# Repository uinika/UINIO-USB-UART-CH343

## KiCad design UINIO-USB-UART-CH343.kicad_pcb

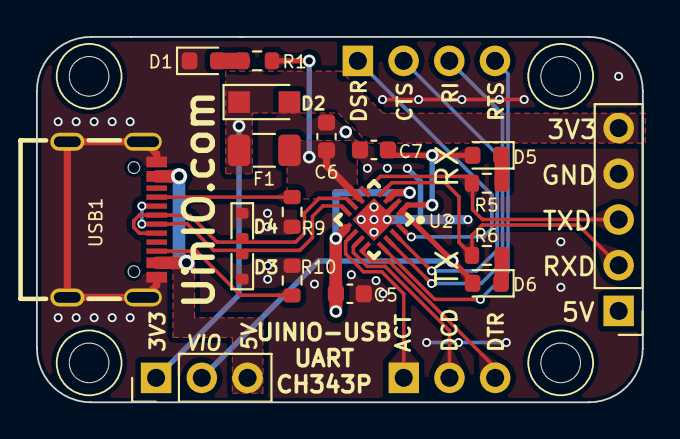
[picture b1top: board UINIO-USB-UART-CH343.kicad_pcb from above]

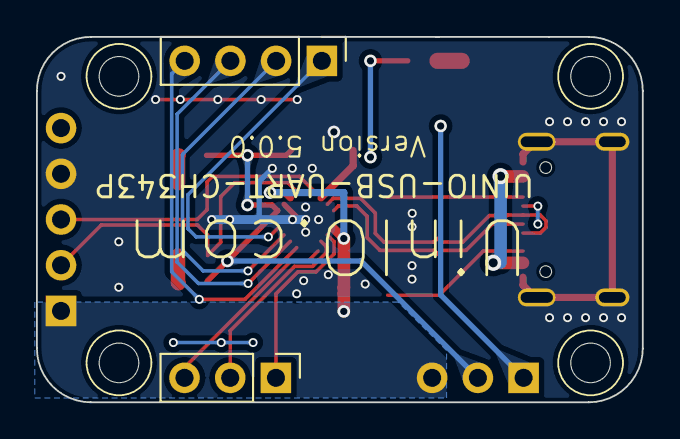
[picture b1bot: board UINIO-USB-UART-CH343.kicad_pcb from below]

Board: 2 copper layers, 33.7 x 20.3 mm, 25 parts (2 on the bottom side), 21 nets.

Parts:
C5, C6: 0.1uF; C_0603_1608Metric
C7: 1uF; C_0603_1608Metric
D1: LED Red; LED_0603_1608Metric
D2: 1N4007; Nexperia_CFP3_SOD-123W
D3, D4: LESD5D5.0CT1G; D_SOD-523
D5, D6: BLUE LED; LED_0603_1608Metric
F1: 60V 1A; Fuse_1206_3216Metric
HOLE**: Hole-2mm
HOLE**#2, HOLE**#3, HOLE**#4: Hole-2mm
J4, J7: Conn_01x03_Pin; PinHeader_1x03_P2.54mm_Vertical
J5: Conn_01x05_Pin; PinHeader_1x05_P2.54mm_Vertical
J6: Conn_01x04_Pin; PinHeader_1x04_P2.54mm_Vertical
R1, R5, R6: 2K; R_0603_1608Metric
R9, R10: 5.1K; R_0603_1608Metric
U2: CH343P; TQFN-16_L3.0-W3.0-P0.50-BL-EP1.7
USB1: USB_Type_C_16Pin; USB-C-SMD_TYPEC-304J-BCP16

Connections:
/CH343_ACT#: J4.1, U2.10 (ACT#)
/CH343_CTS: J6.2, U2.15 (CTS)
/CH343_DCD: J4.2, U2.11 (DCD)
/CH343_DSR: J6.3, U2.14 (DSR)
/CH343_DTR: J4.3, U2.12 (DTRTNOW)
/CH343_RI: J6.1, U2.16 (RI)
/CH343_RTS: J6.4, U2.13 (RTS)
/CH343_RXD: J5.3, R5.1, U2.5 (RXD)
/CH343_TXD: J5.2, R6.1, U2.4 (TXD)
/CH343_USB_Data_N: D3.2 (A2), U2.8 (UD-), USB1.A7 (DN1), USB1.B7 (DN2)
/CH343_USB_Data_P: D4.2 (A2), U2.7 (UD+), USB1.A6 (DP1), USB1.B6 (DP2)
/CH343_V3: C6.2, F1.2, R1.2, U2.6 (V3)
/CH343_VDD_3.3V: D2.1 (K), F1.1, J5.5, J7.1
/CH343_VDD_5V: C5.2, J5.1, J7.3, U2.3 (VDD5), U2.9 (VBUS), USB1.A4B9 (VBUS), USB1.B4A9 (VBUS)
/CH343_VIO: C7.1, D5.2 (A), D6.2 (A), J7.2, U2.1 (VIO)
GND: C5.1, C6.1, C7.2, D1.1 (K), D2.2 (A), D3.1 (A1), D4.1 (A1), J5.4, R9.1, R10.1, U2.2 (GND), U2.17 (EP), USB1.13 (GND), USB1.14 (GND), USB1.15 (GND), USB1.16 (GND), USB1.A1B12 (GND), USB1.B1A12 (GND)
unnamed: D1.2 (A), R1.1
unnamed: D5.1 (K), R5.2
unnamed: D6.1 (K), R6.2
unnamed: R9.2, USB1.A5 (CC1)
unnamed: R10.2, USB1.B5 (CC2)

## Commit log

2025-01-08 Release UINIO-USB-UART-CH343 version 5.0.0.
